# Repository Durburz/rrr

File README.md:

# rrr
reed relay replacement for Onkyo DR-L50 (and others) in the audio path.<br />
!!!These replacements are not intended to be used in the AC power part!!!

replacements for following relays are in this repository:
| REF NO.       | DESCRIPTION   | PART NO.      | ALTERNATIVES  | BRANCH        |
| ------------- | ------------- | ------------- | ------------- | ------------- |
| RL5801        | NRL-2P5A-DC24-164<br />NRL-2P5A-DC24-098<br />NRL-2P5A-DC24-129<br />NRL-2P5A-DC24-142 | 25065636<br />25065517<br />25065563<br />25065586 | ALA2F24<br />(gold plated but discontinued) | [25065636/25065517/25065563/25065586](https://github.com/Durburz/rrr/tree/25065636%2F25065517%2F25065563) |
| RL5802        | NRL-1P3A-DC24-165 | 25065637 | - | [25065637](https://github.com/Durburz/rrr/tree/25065637) |
| RL5803        | NRL-2P5A-DC24-164<br />NRL-2P5A-DC24-098<br />NRL-2P5A-DC24-129<br />NRL-2P5A-DC24-142 | 25065636<br />25065517<br />25065563<br />25065586 | ALA2F24<br />(gold plated but discontinued) | [25065636/25065517/25065563/25065586](https://github.com/Durburz/rrr/tree/25065636%2F25065517%2F25065563) |

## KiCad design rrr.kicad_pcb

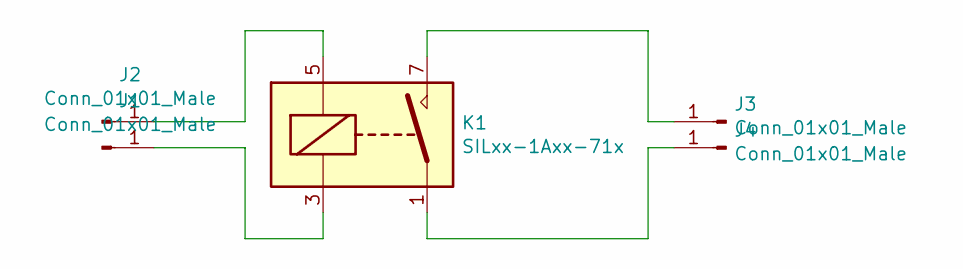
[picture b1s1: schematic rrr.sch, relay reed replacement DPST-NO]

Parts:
J1, J2, J3, J4: Conn_01x01_Male; PinHeader_1x01_P2.54mm_Vertical
K1: SILxx-1Axx-71x; Relay_SPST_StandexMeder_SIL_Form1A

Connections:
unnamed: J1.1, K1.3
unnamed: J2.1, K1.5
unnamed: J3.1, K1.7
unnamed: J4.1, K1.1

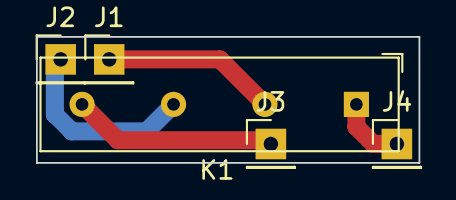
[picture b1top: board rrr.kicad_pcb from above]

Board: 2 copper layers, 21.2 x 7.0 mm, 5 parts (0 on the bottom side), 4 nets.

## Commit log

2021-07-14 Initial commit for 25065636/25065517/25065563
2021-07-14 clean master branch
2021-07-14 Initial commit for 25065637
2021-07-15 Create LICENSE

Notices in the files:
rrr.kicad_pcb:
© 2021 Durburz
